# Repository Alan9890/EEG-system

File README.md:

# EEG-system

NB: If you choose to replicate this project, you do so at your own risk. This is a project that electrically interacts with the human body, and as such there are risks involved. I have designed this system to be as safe as I can make it, but you should still proceed with caution.

This personal project came about as a way to merge two of my interests: physiology and electronics. Electrophysiological signals are the measurable electrical signatures associated with physiological processes. Examples include ECG and EMG for heart and muscle activity respectively. 

## The current state of the project:
Features:
* **Up to 8 channels with 24-bit resolution.** The ADS1298 chip is capable of a maximum of sampling all eight channels at 32k samples/second, but the real limitation is the microcontroller. Practically, a single channel can be broadcast over wifi at about 1000 samples/second. Higher rates can be achieved over a wired connection, or if upgrading the microcontroller.
* **Input referred noise < 5 uV peak-to-peak** (demonstrated to be suitable for EEG, including
SSVEP-based brain-computer interfaces). The system includes up to 12x programmable gain.
* **Battery-powered** for portability, to reduce risk of electric shock, and mitigate contamination from AC noise.
* **Custom GUI** written in Python for device control, data capture, visualization, and analysis
* Capabilities include measuring heart (ECG), muscle (EMG) and brain (EEG) signals.

This repository documents a combination of a python GUI, NodeMCU/arduino code and a PCB design to create a system for acquisition of biological signals. At this point, this project repo includes hardware schematics, circuit board layouts (Eagle CAD files) and firmware (C++), as well as user interface GUI (Python 3.6) which can do the following:
* Connect to a WiFi network and start data collection
* Display real-time readings being collected by the hardware, as well as FFT (frequency spectrum) display.
* Record the time-domain data to a CSV file
* Reset the device
* Toggle the 50 Hz notch filter or high-pass filter on or off
* Change the signal source to choose between the electrodes, the internally generated test signal, or internally shorting the inputs
* Select a different sampling rate, input channel or amplifier gain
* Display the maximum frequency of the signal in the current display window

Below is a photo of the EEG-capturing hardware:

Below is a demo of the system capturing alpha waves over my occipital lobe (red text added):

## Areas of ongoing development:
* The wifi transmission of data could do with improvement. It currently employs the UDP "send and forget" protocol, which includes no error checking. This was required to achieve throughput, but might result in interruption of signal during periods of poor signal reception. It might be better to move to bluetooth for transmission.
* Ability to zoom the real-time or FFT plots to a resolution of interest (e.g if working with EMG then we want to see 500Hz - 1000Hz, but for EEG, usually 100Hz is plenty)
* Display multiple channels at once

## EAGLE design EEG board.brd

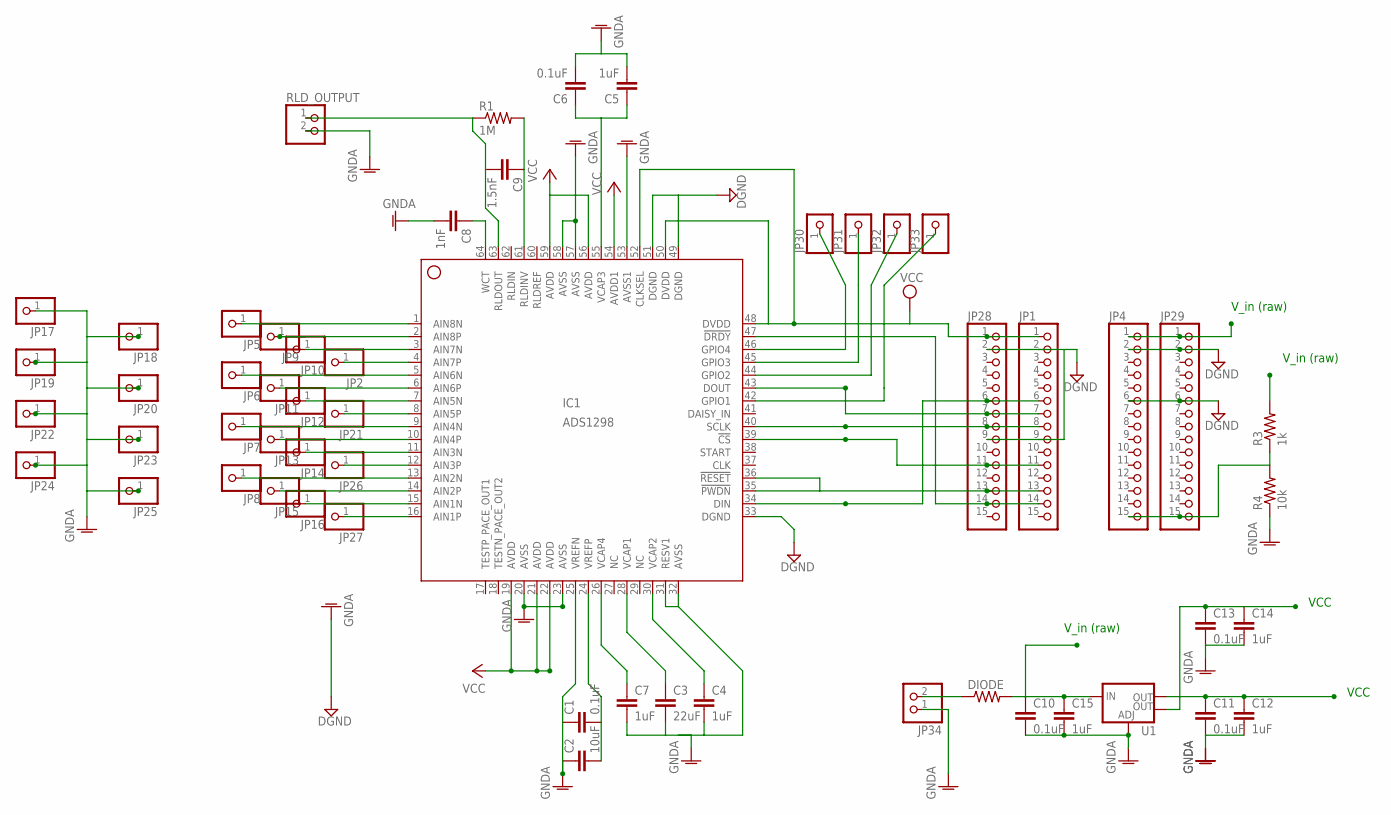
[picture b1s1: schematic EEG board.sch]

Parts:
C1, C6, C10, C11, C13: 0.1uF; C0805
C2: 10uF; C0805
C3: 22uF; C0805
C4, C5, C7, C12, C14, C15: 1uF; C0805
C8: 1nF; C0805
C9: 1.5nF; C0805
DIODE: R-US_R0805; R0805
IC1: ADS1298; HTQFP-64-PAP
JP1, JP4, JP28, JP29: PINHD-1X15; 1X15
JP2, JP5, JP6, JP7, JP8, JP9, JP10, JP11, JP12, JP13, JP14, JP15, JP16, JP17, JP18, JP19, JP20, JP21, JP22, JP23, JP24, JP25, JP26, JP27, JP30, JP31, JP32, JP33: PINHD-1X1; 1X01
JP34: PINHD-1X2; 1X02
R1: 1M; R0805
R3: 1k; R0805
R4: 10k; R0805
RLD_OUTPUT: PINHD-1X2/90; 1X02/90
U1: V_REG_LM1117SOT223; SOT223

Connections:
9V: DIODE.1, JP34.2
AVDD: C11.1, C12.1, IC1.54 (AVDD1), U1.2 (OUT)
AVDD1: C13.1, C14.1, IC1.19 (AVDD), IC1.21 (AVDD), IC1.22 (AVDD), IC1.56 (AVDD), IC1.59 (AVDD), U1.4 (OUT)
AVSS: C1.1, C2.1, C3.2, C4.2, C5.2, C6.2, C7.2, C8.2, C10.2, C11.2, C12.2, C13.2, C14.2, C15.2, IC1.20 (AVSS), IC1.23 (AVSS), IC1.25 (VREFN), IC1.31 (RESV1), IC1.32 (AVSS), IC1.53 (AVSS1), IC1.57 (AVSS), IC1.58 (AVSS), JP4.2, JP17.1, JP18.1, JP19.1, JP20.1, JP22.1, JP23.1, JP24.1, JP25.1, JP29.2, JP34.1, R4.1, RLD_OUTPUT.2, U1.1 (ADJ)
CS: IC1.39 (!CS), JP1.11, JP28.11
DGND: IC1.33 (DGND), IC1.49 (DGND), IC1.51 (DGND), JP1.2, JP1.9, JP4.6, JP28.2, JP28.9, JP29.6
DIN: IC1.34 (DIN), JP1.6, JP28.6
DOUT: IC1.43 (DOUT), JP1.7, JP28.7
DRDY: IC1.47 (!DRDY), JP1.14, JP28.14
DVDD: IC1.48 (DVDD), IC1.50 (DVDD), IC1.52 (CLKSEL), JP1.1, JP28.1
unnamed: IC1.1 (AIN8N), JP5.1
unnamed: IC1.2 (AIN8P), JP9.1
unnamed: IC1.3 (AIN7N), JP10.1
unnamed: IC1.4 (AIN7P), JP2.1
unnamed: IC1.5 (AIN6N), JP6.1
unnamed: IC1.6 (AIN6P), JP11.1
unnamed: IC1.7 (AIN5N), JP12.1
unnamed: IC1.8 (AIN5P), JP21.1
unnamed: IC1.9 (AIN4N), JP7.1
unnamed: IC1.10 (AIN4P), JP13.1
unnamed: IC1.11 (AIN3N), JP14.1
unnamed: IC1.12 (AIN3P), JP26.1
unnamed: IC1.13 (AIN2N), JP8.1
unnamed: IC1.14 (AIN2P), JP15.1
unnamed: IC1.15 (AIN1N), JP16.1
unnamed: IC1.16 (AIN1P), JP27.1
unnamed: C1.2, C2.2, IC1.24 (VREFP)
unnamed: C3.1, IC1.28 (VCAP1)
unnamed: C4.1, IC1.30 (VCAP2)
unnamed: C5.1, C6.1, IC1.55 (VCAP3)
unnamed: C8.1, IC1.64 (WCT)
unnamed: C7.1, IC1.26 (VCAP4)
unnamed: C9.1, IC1.61 (RLDINV), R1.2
unnamed: JP4.15, JP29.15, R3.1, R4.2
unnamed: C9.2, IC1.63 (RLDOUT), R1.1, RLD_OUTPUT.1
unnamed: IC1.45 (GPIO3), JP31.1
unnamed: IC1.44 (GPIO2), JP32.1
unnamed: IC1.42 (GPIO1), JP33.1
unnamed: IC1.46 (GPIO4), JP30.1
PDWN/RESET: IC1.35 (!PWDN), IC1.36 (!RESET), JP1.13, JP28.13
SCLK: IC1.40 (SCLK), JP1.8, JP28.8
VIN: C10.1, C15.1, DIODE.2, JP4.1, JP29.1, R3.2, U1.3 (IN)

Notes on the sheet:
V_in (raw)
VCC

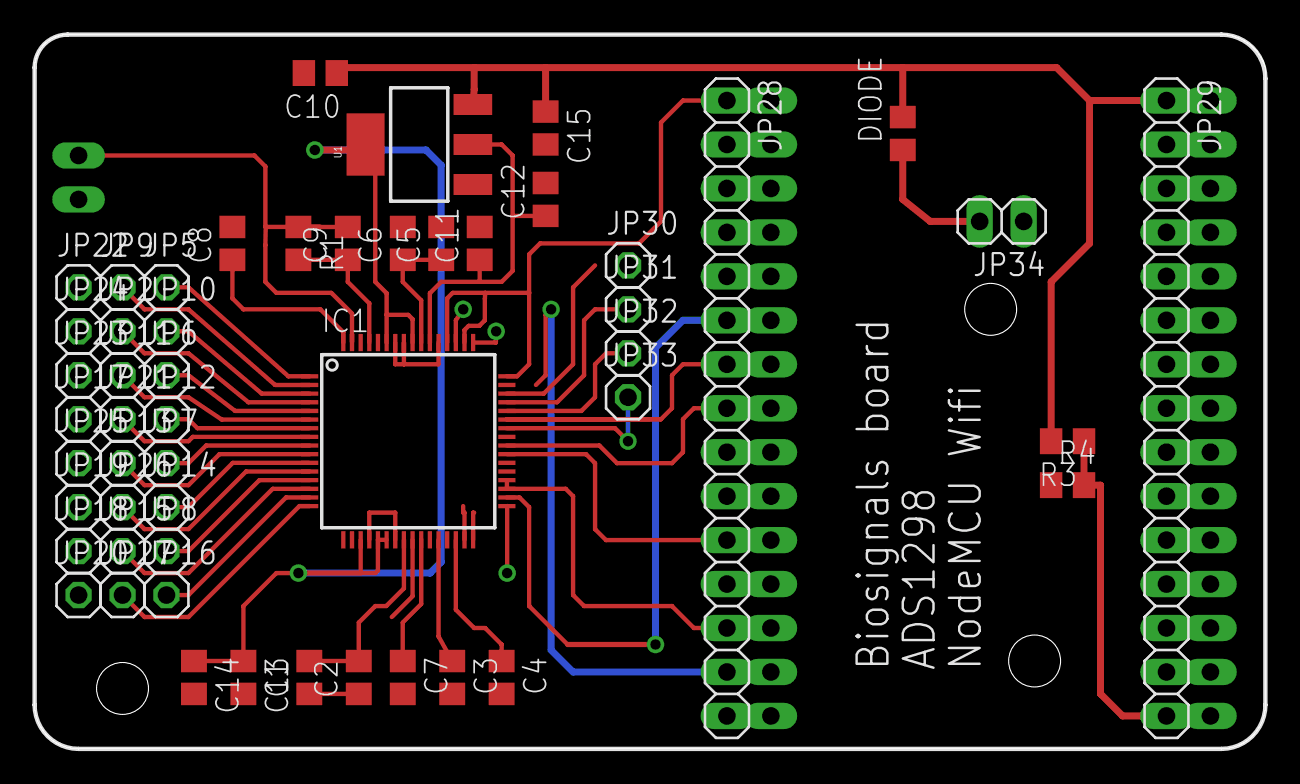
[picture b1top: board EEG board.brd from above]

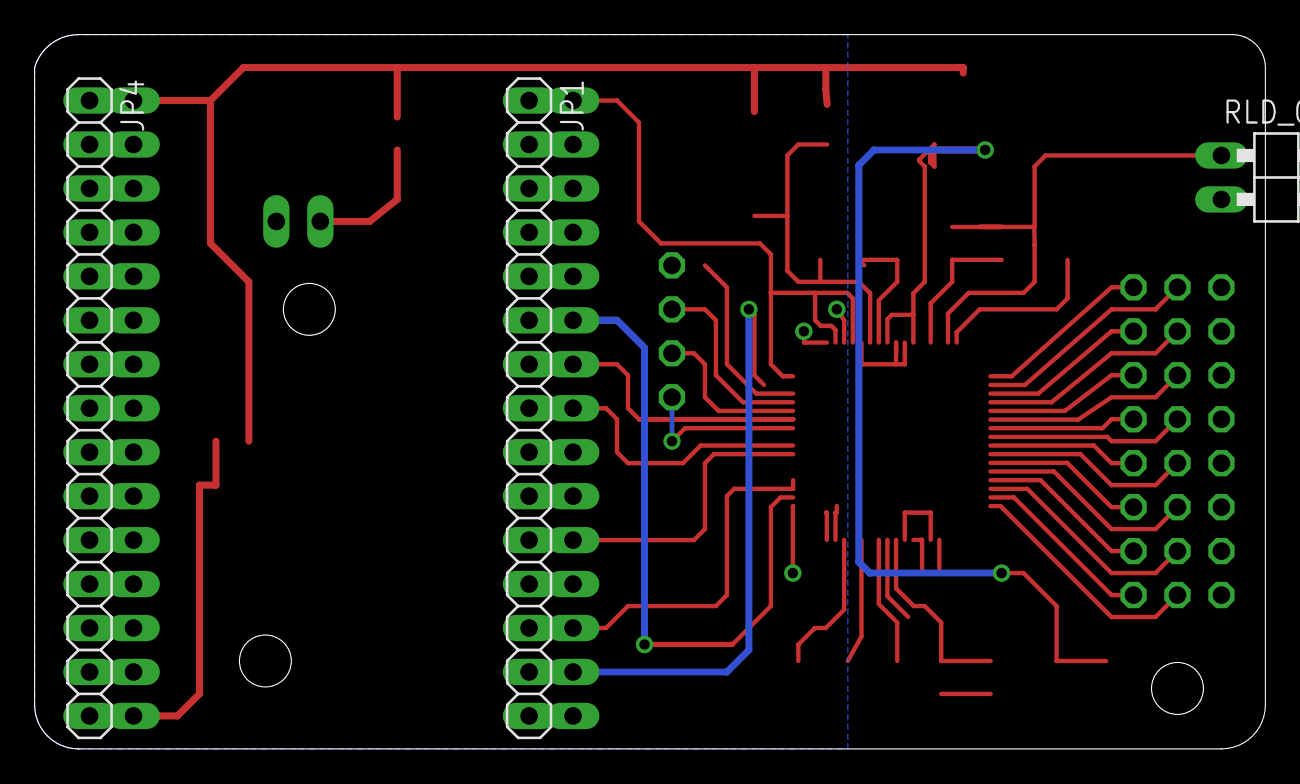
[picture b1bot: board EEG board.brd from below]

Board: 2 copper layers, 71.1 x 41.3 mm, 55 parts (3 on the bottom side), 42 nets.

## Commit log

2017-12-19 Create Python-GUI
2017-12-19 Create NodeMCU-firmware
2017-12-19 Rename Python-GUI to Python-GUI.py
2017-12-19 Rename NodeMCU-firmware to NodeMCU-firmware.ino
2017-12-19 Create Wavelets.py
    Experimental script that pulls data from c:\EEG.txt, and cleans it using a 3rd-level wavelet transform and soft-thresholding on the detail coefficients. The threshold is set to 15% of the respective 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
2018-01-12 Update Python-GUI.py
    Updated connect button callback to include error handling for when there is no wifi connection available. Previously, it would crash the GUI, but now it raises an exception and opens an error dialog 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
2018-01-23 Update Python-GUI.py
    Some minor bug fixes:
    - When changing sampling frequencies, the deque objects for data and time indices were overwritten with regular lists. Thus, the lengths of these lists kept growing as new data was appended, instead 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
    - The method by which the peak frequency was determined, in the update function, was rewritten to use the numpy array method argmax. This is more efficient code.
2018-01-23 Update README.md
    More detail added
2018-08-14 Annotated photo of EEG hardware
2018-08-14 Included photo of hardware
2018-08-14 EEG hardware photo
2018-10-28 Added date to CSV file name
    Also now only creates CSV file when the record button is clicked

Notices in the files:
parts and their libraries:
SparkFun-IC-Power: Licensing: Creative Commons ShareAlike 4.0 International - https://creativecommons.org/licenses/by-sa/4.0
